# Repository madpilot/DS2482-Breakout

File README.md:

View this project on [CADLAB.io](https://cadlab.io/node/820). 

# DS2482 Breakout

Eagle layout for a breakout board for the Maxim DS2482 I2C to 1-wire chip

**This is a work in progress! I just sent the boards off to OSH Park for etching, so I haven't confirmed it _actually_ works yet.**

## Components

* 1 x Maxim DS2482 Single-Channel 1-Wire Master
* 2 x 1.2k SMD resistors (Package: M0805 )

## Pin out of connector (looking component side up, connector on the left)

1. Vcc - Nominally 5V. You can use 3.3V but the pull up resistors probably nned to be changed
2. 1-wire - the 1-wire network wire
3. Ground.
4. The SCL pin on the I2C interface
5. The SDA pin on the I2C interface

## Ardiuno Sample code

Coming soon...

## References

https://www.maximintegrated.com/en/products/interface/controllers-expanders/DS2482-100.html

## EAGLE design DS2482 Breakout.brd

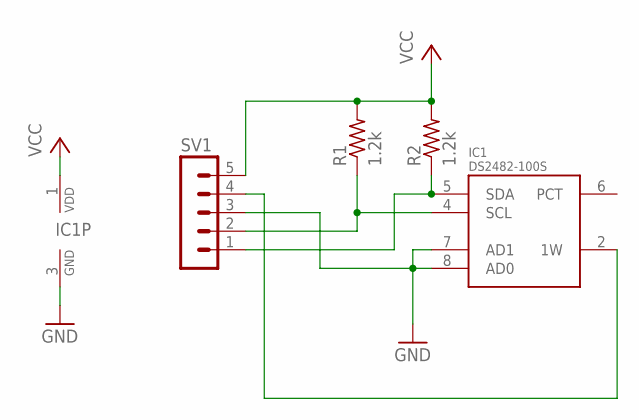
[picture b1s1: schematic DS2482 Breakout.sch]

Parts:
IC1: DS2482-100S; SO08
R1, R2: 1.2k; M0805
SV1: MA05-1

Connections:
GND: IC1.3 (GND), IC1.7 (AD1), IC1.8 (AD0), SV1.3
unnamed: IC1.2 (1W), SV1.4
SCL: IC1.4 (SCL), R1.1, SV1.2
SDA: IC1.5 (SDA), R2.1, SV1.1
VCC: IC1.1 (VDD), R1.2, R2.2, SV1.5

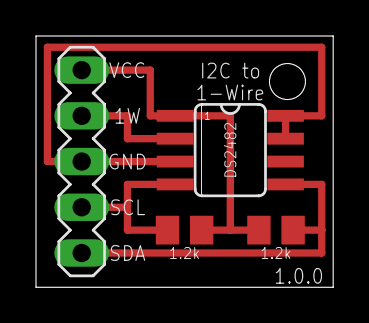
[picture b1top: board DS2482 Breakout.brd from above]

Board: 2 copper layers, 16.5 x 14.0 mm, 4 parts (0 on the bottom side), 5 nets.

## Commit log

2015-11-02 Checkin v1.0.0
2015-11-02 Adding reference to Eagle
2015-11-02 Updating README
2015-11-02 Updating board images
2015-11-02 Fixing typo
2018-04-03 Backlink to CADLAB.io has been added.
